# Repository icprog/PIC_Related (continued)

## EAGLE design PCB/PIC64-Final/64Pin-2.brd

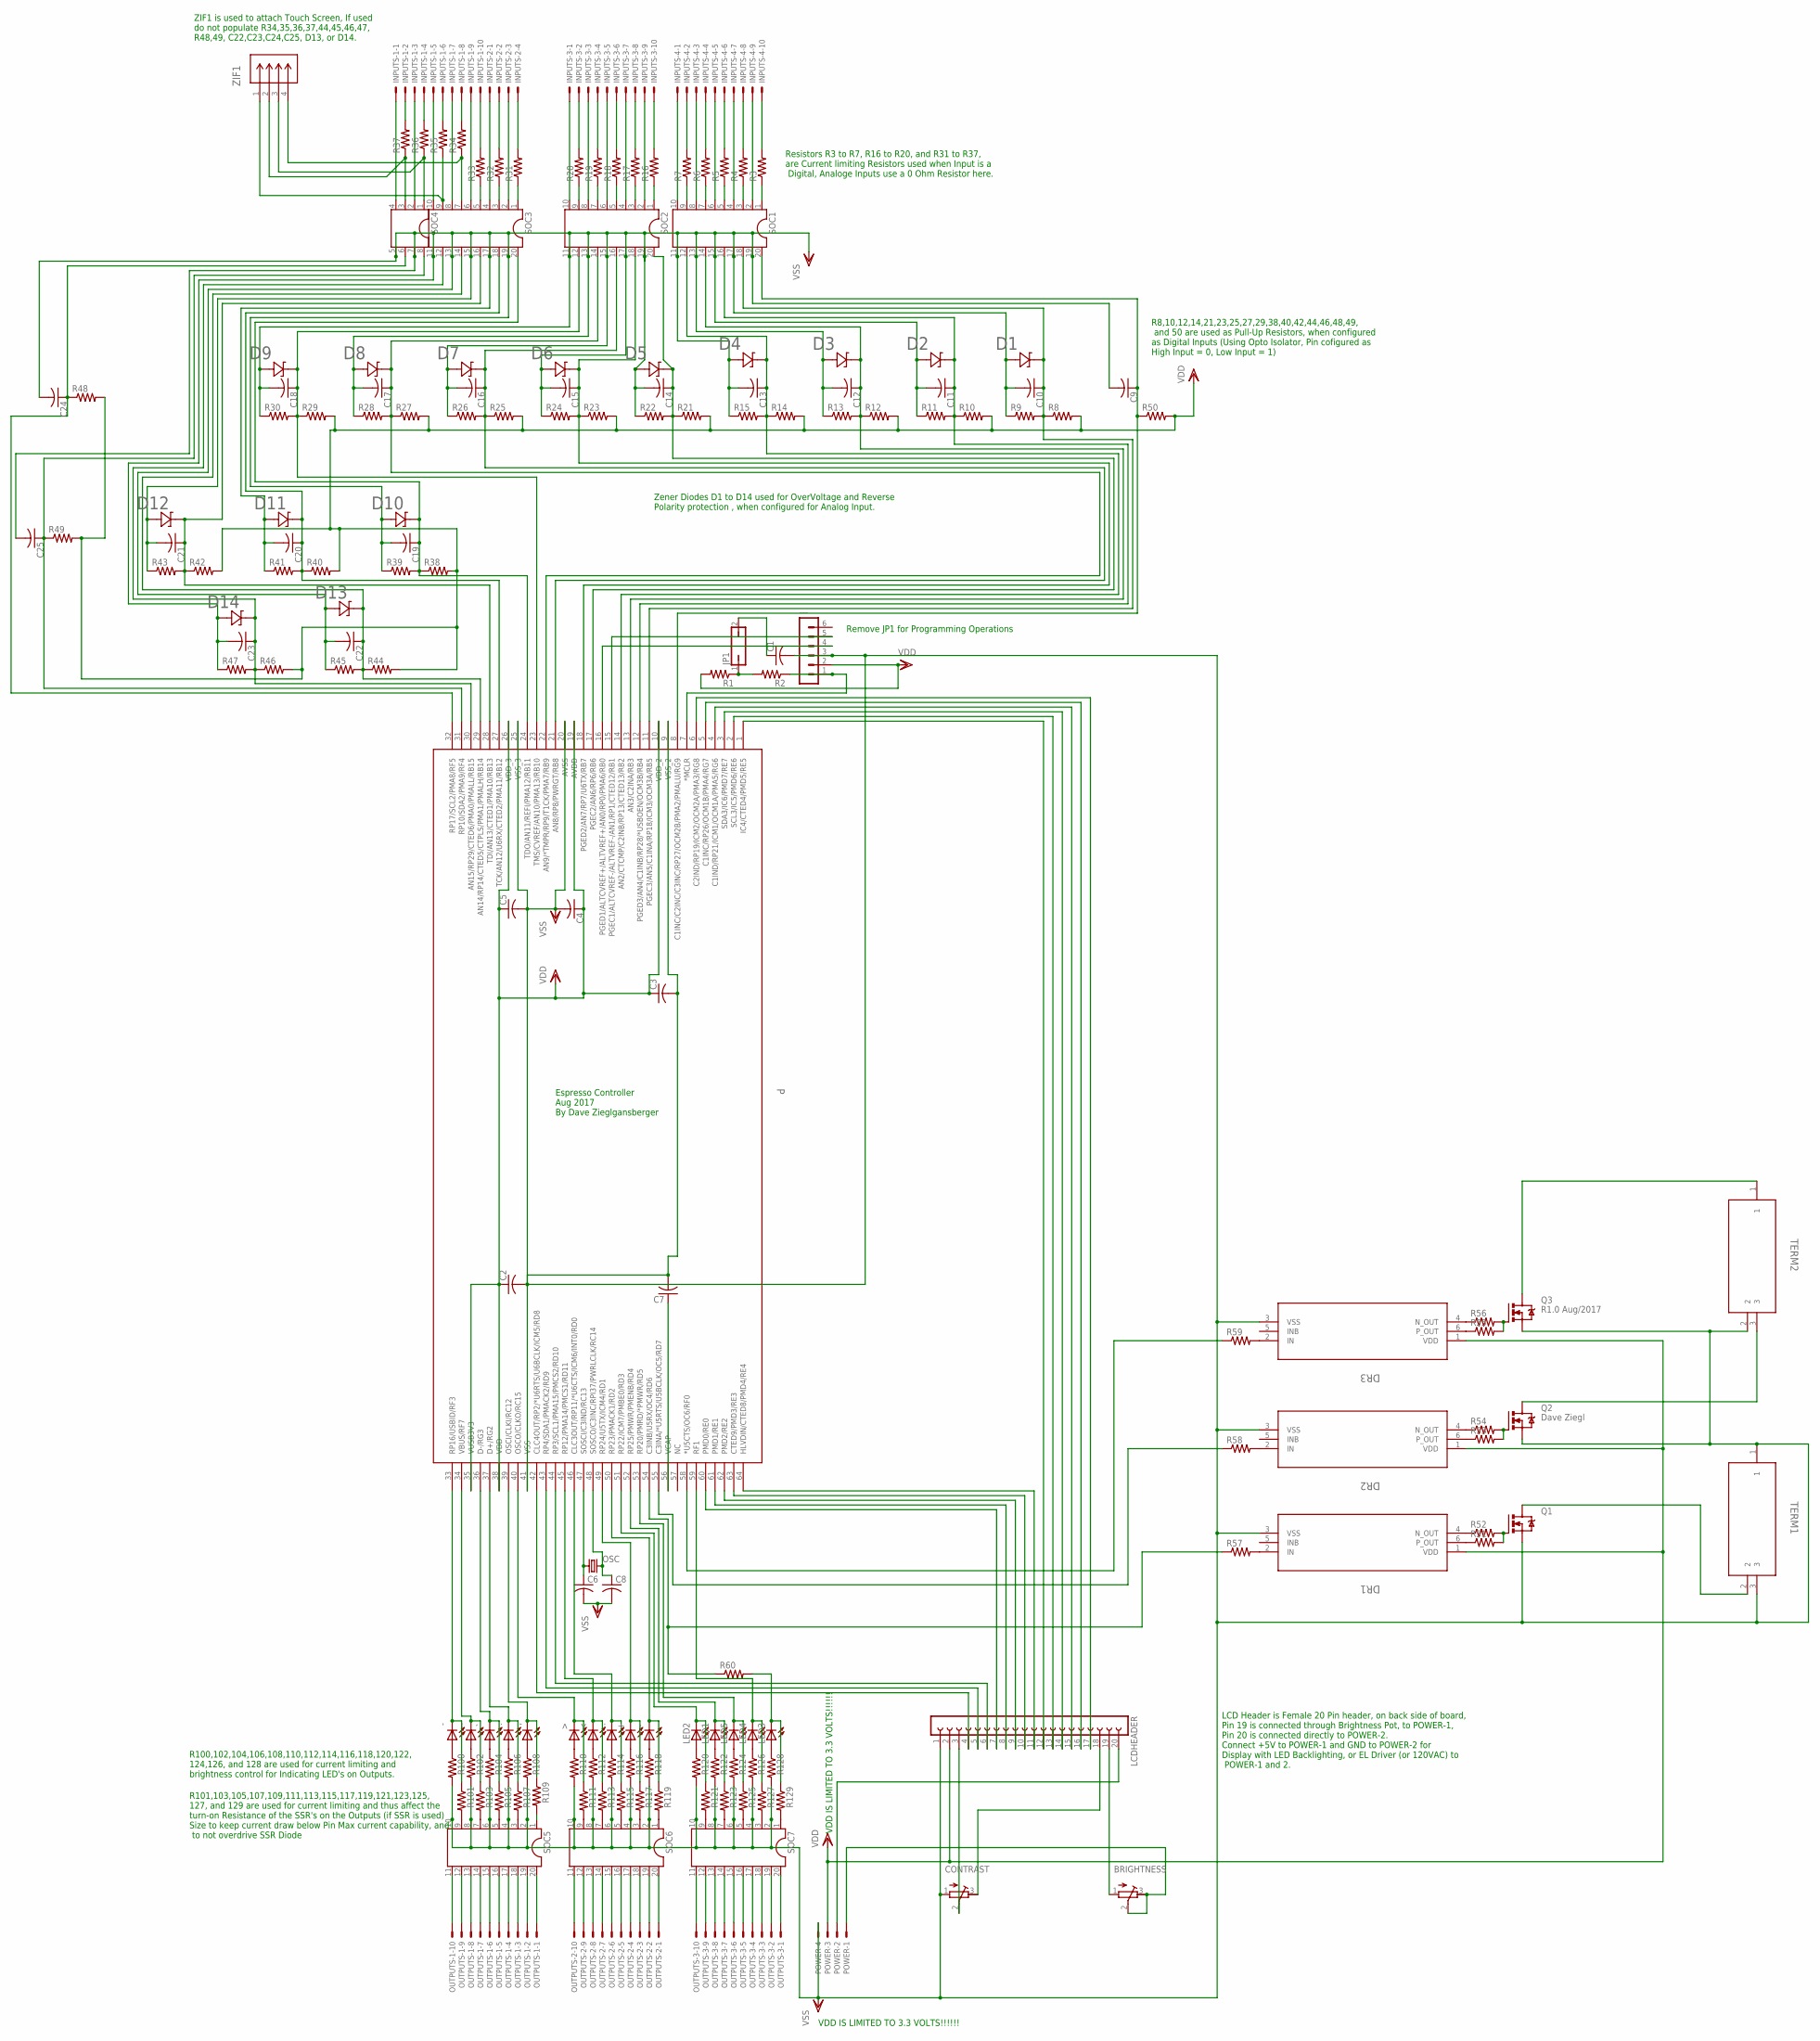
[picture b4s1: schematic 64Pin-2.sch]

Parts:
+: LED_SML0603
,: LED_SML0603
-: LED_SML0603
--: LED_SML0603
---: MA06-1
., ..: LED_SML0603
<: LED_SML0603
>: LED_SML0603
BRIGHTNESS: RTRIM3296W
C1, C2, C3, C4, C5, C6, C7, C8, C9, C10, C11, C12, C13, C14, C15, C16, C17, C18, C19, C20, C21, C22, C23, C24, C25: C0603
CONTRAST: RTRIM3296W
D1, D2, D3, D4, D5, D6, D7, D8, D9, D10, D11, D12, D13, D14: CZRU-M
DR1, DR2, DR3: MF06A
INPUTS-1, INPUTS-3, INPUTS-4: 22-23-2101
INPUTS-2: 22-23-2041
JP1: JP1
LCDHEADER: FE20
LED1, LED2, LED3, LED4, LED5: LED_SML0603
OSC: TC26H
OUTPUTS-1, OUTPUTS-2, OUTPUTS-3: 22-23-2101
P: TQFP64_10X10MC
POWER: 22-23-2041
Q1: TO220BV
Q2: Dave Ziegl; TO220BV
Q3: R1.0 Aug/2017; TO220BV
R1, R2, R3, R4, R5, R6, R7, R8, R9, R10, R11, R12, R13, R14, R15, R16, R17, R18, R19, R20, R21, R22, R23, R24, R25, R26, R27, R28, R29, R30, R31, R32, R33, R34, R35, R36, R37, R38, R39, R40, R41, R42, R43, R44, R45, R46, R47, R48, R49, R50, R51, R52, R53, R54, R55, R56, R57, R58, R59, R60, R100, R101, R102, R103, R104, R105, R106, R107, R108, R109, R110, R111, R112, R113, R114, R115, R116, R117, R118, R119, R120, R121, R122, R123, R124, R125, R126, R127, R128, R129: R0603
SOC1, SOC2, SOC3, SOC5, SOC6, SOC7: DIL20
SOC4: DIL08
TERM1, TERM2: 282837-3
ZIF1: 84952-4; CON4_SMT-RA_FCC-FPC2
`: LED_SML0603
~: LED_SML0603

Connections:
MCLR: ---.1, P.7 (*MCLR), R2.1
unnamed: INPUTS-1.1, SOC4.4
unnamed: R101.2, SOC5.9
unnamed: JP1.1, R1.1, R2.2
unnamed: INPUTS-1.2, R37.2
unnamed: R103.2, SOC5.7
unnamed: INPUTS-1.3, SOC4.2
unnamed: R105.2, SOC5.5
unnamed: INPUTS-1.4, R36.2
unnamed: R107.2, SOC5.3
unnamed: INPUTS-1.5, SOC3.10
unnamed: R36.1, SOC4.1, ZIF1.3
unnamed: C1.1, JP1.2
unnamed: R37.1, SOC4.3, ZIF1.2
unnamed: INPUTS-1.6, R35.2
unnamed: INPUTS-1.7, SOC3.8
unnamed: INPUTS-1.8, R34.2
unnamed: INPUTS-1.9, SOC3.6
unnamed: R109.2, SOC5.1
unnamed: INPUTS-1.10, R33.2
unnamed: INPUTS-2.1, SOC3.4
unnamed: INPUTS-2.2, R32.2
unnamed: INPUTS-2.3, SOC3.2
unnamed: INPUTS-2.4, R31.2
unnamed: DR2.4 (N_OUT), R54.1
unnamed: DR2.6 (P_OUT), R53.1
unnamed: DR1.4 (N_OUT), R52.1
unnamed: -.A, R100.1
unnamed: --.A, R102.1
unnamed: R104.1, `.A
unnamed: ..A, R106.1
unnamed: ,.A, R108.1
unnamed: DR1.6 (P_OUT), R51.1
unnamed: >.A, R110.1
unnamed: R111.2, SOC6.9
unnamed: INPUTS-4.5, SOC1.6
unnamed: INPUTS-4.4, R6.2
unnamed: Q3.D, TERM2.1
unnamed: R113.2, SOC6.7
unnamed: Q1.G, R51.2, R52.2
unnamed: R115.2, SOC6.5
unnamed: Q2.G, R53.2, R54.2
unnamed: R117.2, SOC6.3
unnamed: DR3.4 (N_OUT), R56.1
unnamed: R119.2, SOC6.1
unnamed: R6.1, SOC1.7
unnamed: R118.1, ~.A
unnamed: +.A, R116.1
unnamed: ...A, R114.1
unnamed: <.A, R112.1
unnamed: DR3.6 (P_OUT), R55.1
unnamed: R121.2, SOC7.9
unnamed: Q3.G, R55.2, R56.2
unnamed: R123.2, SOC7.7
unnamed: LCDHEADER.20, POWER.2
unnamed: R125.2, SOC7.5
unnamed: Q2.D, TERM2.3
unnamed: R127.2, SOC7.3
unnamed: R129.2, SOC7.1
unnamed: LED3.A, R128.1
unnamed: LED4.A, R126.1
unnamed: LED5.A, R124.1
unnamed: LED1.A, R122.1
unnamed: LED2.A, R120.1
unnamed: Q1.D, TERM1.2
unnamed: BRIGHTNESS.1 (A), LCDHEADER.19
unnamed: BRIGHTNESS.2 (S), BRIGHTNESS.3 (E), POWER.1
unnamed: DR1.2 (IN), R57.2
unnamed: DR2.2 (IN), R58.2
unnamed: DR3.2 (IN), R59.2
unnamed: P.55 (C3INA/*U5RTS/U5BCLK/OC5/RD7), R58.1
unnamed: P.58 (*U5CTS/OC6/RF0), R59.1
unnamed: R35.1, SOC3.9, ZIF1.1
unnamed: R34.1, SOC3.7, ZIF1.4
unnamed: R33.1, SOC3.5
unnamed: R32.1, SOC3.3
unnamed: R31.1, SOC3.1
unnamed: INPUTS-3.1, SOC2.10
unnamed: R20.1, SOC2.9
unnamed: INPUTS-3.3, SOC2.8
unnamed: INPUTS-3.2, R20.2
unnamed: INPUTS-3.4, R19.2
unnamed: INPUTS-3.5, SOC2.6
unnamed: R19.1, SOC2.7
unnamed: INPUTS-3.7, SOC2.4
unnamed: R17.1, SOC2.3
unnamed: INPUTS-3.8, R17.2
unnamed: INPUTS-3.9, SOC2.2
unnamed: R16.1, SOC2.1
unnamed: INPUTS-3.10, R16.2
unnamed: INPUTS-4.1, SOC1.10
unnamed: INPUTS-4.2, R7.2
unnamed: R7.1, SOC1.9
unnamed: INPUTS-4.3, SOC1.8
unnamed: R18.1, SOC2.5
unnamed: INPUTS-3.6, R18.2
unnamed: INPUTS-4.6, R5.2
unnamed: R5.1, SOC1.5
unnamed: INPUTS-4.7, SOC1.4
unnamed: INPUTS-4.8, R4.2
unnamed: R4.1, SOC1.3
unnamed: INPUTS-4.9, SOC1.2
unnamed: INPUTS-4.10, R3.2
unnamed: R3.1, SOC1.1
unnamed: CONTRAST.2 (S), LCDHEADER.3
unnamed: CONTRAST.3 (E), LCDHEADER.18
OUT: LED3.C, R60.2, R129.1
OUT1-1: OUTPUTS-1.10, SOC5.11
OUT1-2: OUTPUTS-1.9, SOC5.12
OUT2-1: OUTPUTS-1.8, SOC5.13
OUT2-2: OUTPUTS-1.7, SOC5.14
OUT3-1: OUTPUTS-1.6, SOC5.15
OUT3-2: OUTPUTS-1.5, SOC5.16
OUT4-1: OUTPUTS-1.4, SOC5.17
OUT4-2: OUTPUTS-1.3, SOC5.18
OUT5-1: OUTPUTS-1.2, SOC5.19
OUT5-2: OUTPUTS-1.1, SOC5.20
OUT6-1: OUTPUTS-2.10, SOC6.11
OUT6-2: OUTPUTS-2.9, SOC6.12
OUT7-1: OUTPUTS-2.8, SOC6.13
OUT7-2: OUTPUTS-2.7, SOC6.14
OUT8-1: OUTPUTS-2.6, SOC6.15
OUT8-2: OUTPUTS-2.5, SOC6.16
OUT9-1: OUTPUTS-2.4, SOC6.17
OUT9-2: OUTPUTS-2.3, SOC6.18
OUT10-1: OUTPUTS-2.2, SOC6.19
OUT10-2: OUTPUTS-2.1, SOC6.20
OUT11-1: OUTPUTS-3.10, SOC7.11
OUT11-2: OUTPUTS-3.9, SOC7.12
OUT12-1: OUTPUTS-3.8, SOC7.13
OUT12-2: OUTPUTS-3.7, SOC7.14
OUT13-1: OUTPUTS-3.6, SOC7.15
OUT13-2: OUTPUTS-3.5, SOC7.16
OUT14-1: OUTPUTS-3.4, SOC7.17
OUT14-2: OUTPUTS-3.3, SOC7.18
OUT15-1: OUTPUTS-3.2, SOC7.19
OUT15-2: OUTPUTS-3.1, SOC7.20
PGEC1: ---.5, P.15 (PGEC1/ALTCVREF-/ALTVREF-/AN1/RP1/CTED12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)
PGECD: ---.4, P.16 (PGED1/ALTCVREF+/ALTVREF+/AN0/RP0/PMA6/R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)
PIN1: LCDHEADER.12, P.1 (IC4/CTED4/PMD5/RE5)
PIN2: LCDHEADER.13, P.2 (SCL3/IC5/PMD6/RE6)
PIN3: LCDHEADER.14, P.3 (SDA3/IC6/PMD7/RE7)
PIN4: LCDHEADER.15, P.4 (C1IND/RP21/ICM1/OCM1A/PMA5/RG6)
PIN5: LCDHEADER.16, P.5 (C1INC/RP26/OCM1B/PMA4/RG7)
PIN6: LCDHEADER.17, P.6 (C2IND/RP19/ICM2/OCM2A/PMA3/RG8)
PIN8: C9.1, P.8 (C1INC/C2INC/C3INC/RP27/OCM2B/PMA2/PMALU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), R50.1, SOC1.20
PIN11: C10.1, D1.1 (11), P.11 (PGEC3/AN5/C1INA/RP18/ICM3/OCM3A/RB5), R8.1, R9.2, SOC1.18
PIN12: C11.1, D2.1 (11), P.12 (PGED3/AN4/C1INB/RP28/*USBOEN/OCM3B/RB4), R10.1, R11.2, SOC1.16
PIN13: C12.1, D3.1 (11), P.13 (AN3/C2INA/RB3), R12.1, R13.2, SOC1.14
PIN14: C13.1, D4.1 (11), P.14 (AN2/CTCMP/C2INB/RP13/CTED13/RB2), R14.1, R15.2, SOC1.12
PIN17: C14.1, D5.1 (11), P.17 (PGEC2/AN6/RP6/RB6), R21.1, R22.2, SOC2.20
PIN18: C15.1, D6.1 (11), P.18 (PGED2/AN7/RP7/U6TX/RB7), R23.1, R24.2, SOC2.18
PIN21: C16.1, D7.1 (11), P.21 (AN8/RP8/PWRGT/RB8), R25.1, R26.2, SOC2.16
PIN22: C17.1, D8.1 (11), P.22 (AN9/*TMPR/RP9/T1CK/PMA7/RB9), R27.1, R28.2, SOC2.14
PIN23: C18.1, D9.1 (11), P.23 (TMS/CVREF/AN10/PMA13/RB10), R29.1, R30.2, SOC2.12
PIN24: C19.1, D10.1 (11), P.24 (TDO/AN11/REFI/PMA12/RB11), R38.1, R39.2, SOC3.20
PIN27: C20.1, D11.1 (11), P.27 (TCK/AN12/U6RX/CTED2/PMA11/RB12), R40.1, R41.2, SOC3.18
PIN28: C21.1, D12.1 (11), P.28 (TDI/AN13/CTED1/PMA10/RB13), R42.1, R43.2, SOC3.16
PIN29: C22.1, D13.1 (11), P.29 (AN14/RP14/CTED5/CTPLS/PMA1/PMALH/RB14), R44.1, R45.2, SOC3.14
PIN30: C23.1, D14.1 (11), P.30 (AN15/RP29/CTED6/PMA0/PMALL/RB15), R46.1, R47.2, SOC3.12
PIN31: C25.1, P.31 (RP10/SDA2/PMA9/RF4), R49.1, SOC4.8
PIN32: C24.1, P.32 (RP17/SCL2/PMA8/RF5), R48.1, SOC4.6
PIN33: -.C, P.33 (RP16/USBID/RF3), R101.1
PIN34: --.C, P.34 (VBUS/RF7), R103.1
PIN36: P.36 (D-/RG3), R105.1, `.C
PIN37: ..C, P.37 (D+/RG2), R107.1
PIN39: ,.C, P.39 (OSCI/CLKI/RC12), R109.1
PIN40: >.C, P.40 (OSCO/CLKO/RC15), R111.1
PIN42: LCDHEADER.4, P.42 (CLC4OUT/RP2/*U6RTS/U6BCLK/ICM5/RD8)
PIN43: LCDHEADER.5, P.43 (RP4/SDA1/PMACK2/RD9)
PIN44: LCDHEADER.6, P.44 (RP3/SCL1/PMA15/PMCS2/RD10)
PIN45: <.C, P.45 (RP12/PMA14/PMCS1/RD11), R113.1
PIN46: ...C, P.46 (CLC3OUT/RP11/*U6CTS/ICM6/INT0/RD0), R115.1
PIN49: +.C, P.49 (RP24/U5TX/ICM4/RD1), R117.1
PIN50: P.50 (RP23/PMACK1/RD2), R119.1, ~.C
PIN51: LED2.C, P.51 (RP22/ICM7/PMBE0/RD3), R121.1
PIN52: LED1.C, P.52 (RP25/PMWR/PMENB/RD4), R123.1
PIN53: LED5.C, P.53 (RP20/PMRD/*PMWR/RD5), R125.1
PIN54: P.54 (C3INB/U5RX/OC4/RD6), R57.1, R60.1
PIN59: LED4.C, P.59 (RF1), R127.1
PIN60: LCDHEADER.7, P.60 (PMD0/RE0)
PIN61: LCDHEADER.8, P.61 (PMD1/RE1)
PIN62: LCDHEADER.9, P.62 (PMD2/RE2)
PIN63: LCDHEADER.10, P.63 (CTED9/PMD3/RE3)
PIN64: LCDHEADER.11, P.64 (HLVDIN/CTED8/PMD4/RE4)
SOSCI: C6.1, OSC.1, P.47 (SOSCI/C3IND/RC13)
SOSCO: C8.1, OSC.2, P.48 (SOSCO/C3INC/RPI37/PWRLCLK/RC14)
VCAP: C7.1, P.56 (VCAP)
VDD: ---.2, C2.1, C3.1, C4.1, C5.1, DR1.1 (VDD), DR2.1 (VDD), DR3.1 (VDD), LCDHEADER.2, P.10 (VDD_2), P.19 (AVDD), P.26 (VDD_3), P.35 (VUSB3V3), P.38 (VDD), POWER.3, R1.2, R8.2, R10.2, R12.2, R14.2, R21.2, R23.2, R25.2, R27.2, R29.2, R38.2, R40.2, R42.2, R44.2, R46.2, R48.2, R49.2, R50.2
VSS: ---.3, C1.2, C2.2, C3.2, C4.2, C5.2, C6.2, C7.2, C8.2, C9.2, C10.2, C11.2, C12.2, C13.2, C14.2, C15.2, C16.2, C17.2, C18.2, C19.2, C20.2, C21.2, C22.2, C23.2, C24.2, C25.2, CONTRAST.1 (A), D1.2 (22), D2.2 (22), D3.2 (22), D4.2 (22), D5.2 (22), D6.2 (22), D7.2 (22), D8.2 (22), D9.2 (22), D10.2 (22), D11.2 (22), D12.2 (22), D13.2 (22), D14.2 (22), DR1.3 (VSS), DR2.3 (VSS), DR3.3 (VSS), LCDHEADER.1, P.9 (VSS_2), P.20 (AVSS), P.25 (VSS_3), P.41 (VSS), POWER.4, Q1.S, Q2.S, Q3.S, R9.1, R11.1, R13.1, R15.1, R22.1, R24.1, R26.1, R28.1, R30.1, R39.1, R41.1, R43.1, R45.1, R47.1, R100.2, R102.2, R104.2, R106.2, R108.2, R110.2, R112.2, R114.2, R116.2, R118.2, R120.2, R122.2, R124.2, R126.2, R128.2, SOC1.11, SOC1.13, SOC1.15, SOC1.17, SOC1.19, SOC2.11, SOC2.13, SOC2.15, SOC2.17, SOC2.19, SOC3.11, SOC3.13, SOC3.15, SOC3.17, SOC3.19, SOC4.5, SOC4.7, SOC5.2, SOC5.4, SOC5.6, SOC5.8, SOC5.10, SOC6.2, SOC6.4, SOC6.6, SOC6.8, SOC6.10, SOC7.2, SOC7.4, SOC7.6, SOC7.8, SOC7.10, TERM1.1, TERM1.3, TERM2.2

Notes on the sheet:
Espresso Controller Aug 2017 By Dave Zieglgansberger
Resistors R3 to R7, R16 to R20, and R31 to R37, are Current limiting Resistors used when Input is a Digital, Analoge Inputs use a 0 Ohm Resistor here.
Remove JP1 for Programming Operations
Zener Diodes D1 to D14 used for OverVoltage and Reverse Polarity protection , when configured for Analog Input.
ZIF1 is used to attach Touch Screen, If used do not populate R34,35,36,37,44,45,46,47, R48,49, C22,C23,C24,C25, D13, or D14.
R8,10,12,14,21,23,25,27,29,38,40,42,44,46,48,49, and 50 are used as Pull-Up Resistors, when configured as Digital Inputs (Using Opto Isolator, Pin cofigured as High Input = 0, Low Input = 1)
LCD Header is Female 20 Pin header, on back side of board, Pin 19 is connected through Brightness Pot, to POWER-1, Pin 20 is connected directly to POWER-2. Connect +5V to POWER-1 and GND to POWER-2 for Display with LED Backlighting, or EL Driver (or 120VAC) to POWER-1 and 2.
R100,102,104,106,108,110,112,114,116,118,120,122, 124,126, and 128 are used for current limiting and brightness control for Indicating LED's on Outputs.
R101,103,105,107,109,111,113,115,117,119,121,123,125, 127, and 129 are used for current limiting and thus affect the turn-on Resistance of the SSR's on the Outputs (if SSR is used) Size to keep current draw below Pin Max current capability, and to not overdrive SSR Diode
VDD IS LIMITED TO 3.3 VOLTS!!!!!!

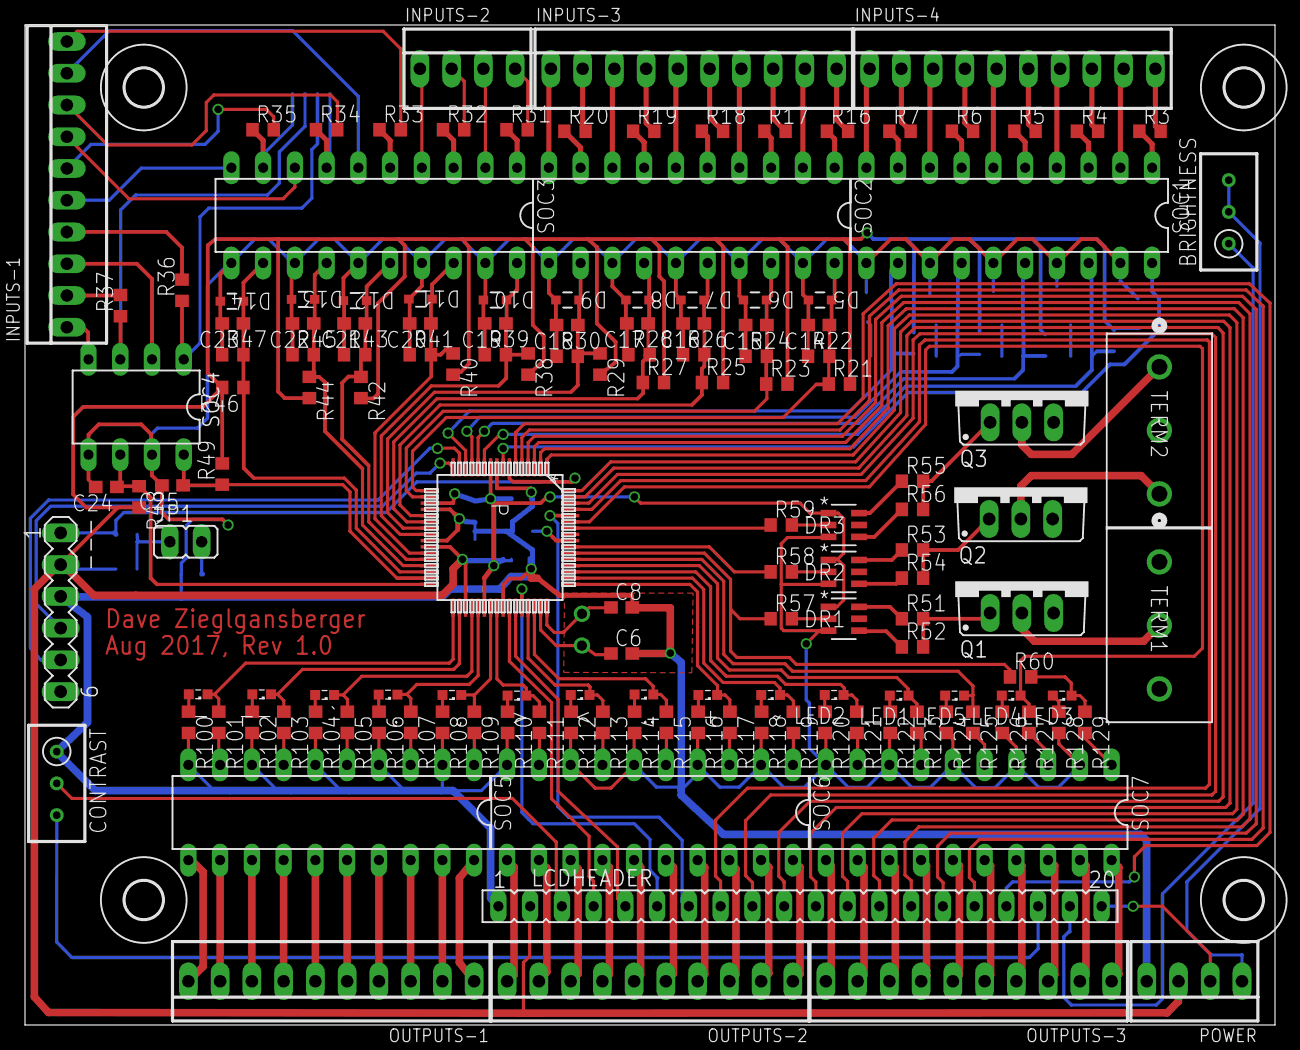
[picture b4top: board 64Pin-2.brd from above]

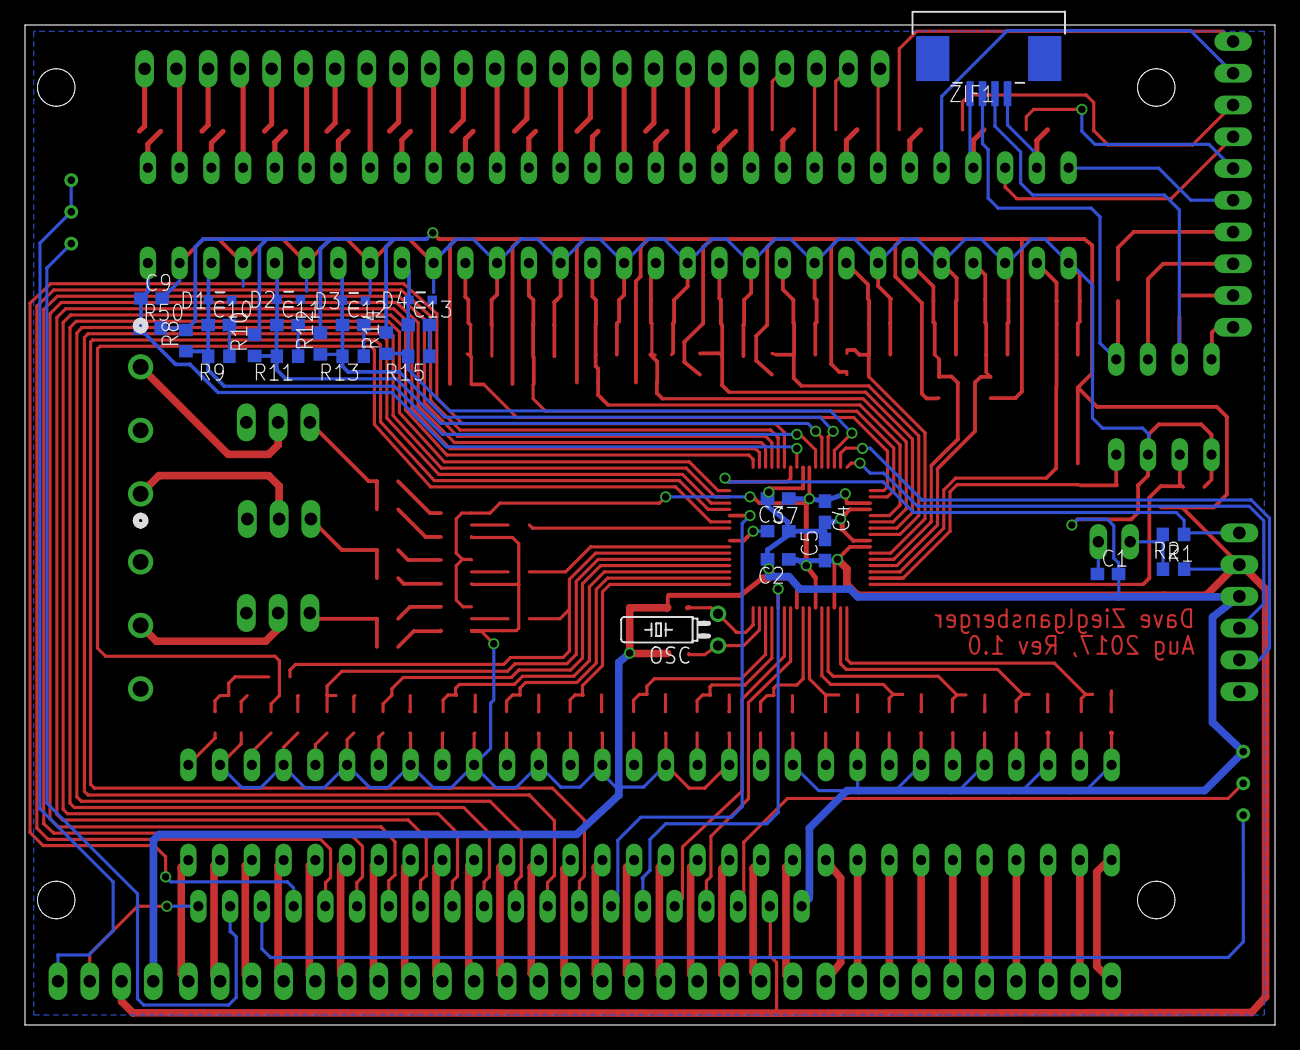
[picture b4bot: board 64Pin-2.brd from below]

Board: 2 copper layers, 100.0 x 80.0 mm, 179 parts (28 on the bottom side), 190 nets.

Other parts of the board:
U$5, U$6, U$7, U$8: 3,0

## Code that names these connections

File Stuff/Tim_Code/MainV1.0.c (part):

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void (display_ADC_count_on_LEDs)(int temp){
    
if (temp > 150){
    RB0 = 1;
} 
else RB0 = 0;

if (temp > 300){
    RB1 = 1;
} 
else RB1 = 0;

if (temp > 450){
    RB2 = 1;
} 
else RB2 = 0;

if (temp > 600){
    RB3 = 1;
} 
else RB3 = 0;

if (temp > 750){
    RB4 = 1;
} 
else RB4 = 0;    
    
if (temp > 1000){
//    RB5 = 1;
} 
//else RB5 = 0;    
    
    
    
}
void display_temperature_on_LEDs(float temp){
if (temp > 200){
    RB0 = 1;
} 
else RB0 = 0;

if (temp > 220){
    RB1 = 1;
} 
else RB1 = 0;

if (temp > 240){
    RB2 = 1;
} 
else RB2 = 0;

if (temp > 260){
    RB3 = 1;
} 
else RB3 = 0;

if (temp > 280){
    RB4 = 1;
} 
else RB4 = 0;    
    
if (temp > 300){
//    RB5 = 1;
} 
//else RB5 = 0;    
    
    
    
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
void display_temperature_on_LEDs2(float temp){
if (temp > 230){
    RB0 = 1;
} 
else RB0 = 0;

if (temp > 240){
    RB1 = 1;
} 
else RB1 = 0;

if (temp > 250){
    RB2 = 1;
} 
else RB2 = 0;

if (temp > 260){
    RB3 = 1;
} 
else RB3 = 0;

if (temp > 270){
    RB4 = 1;
} 
else RB4 = 0;    
    
if (temp > 280){
//    RB5 = 1;
} 
//else RB5 = 0;    
    
    
    
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    char dummy_char = 0;
    temp = temp / 10;
    byte_1 = (char) temp;
//   RC0 = 0; 
   __delay_us(100);
   dummy_char = (SPI_TRANSFER)(byte_1);
   __delay_us(100);
//   RC0 = 1;


}
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    
    //Beginning of RA4 input Switch debounce code
    if ((RA4 == 0) && (button_array[0][3] == 0)){  //0 equals button depressed and button_array[0][3] is for off bit latch
        button_array[0][2] = 1; //[x][y] x = switch 1(RA4) y = on bit active (switch one latched or active)
    }
    if (button_array[0][2] == 1){
        button_array[0][0]++;   //[x][y] x = switch 1(RA4) y = latched on timer
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        }
    }
    if ((button_array[0][0] > 5) && (RA4 == 1)){ //check if latched on timer has expired and button no longer depressed
        button_array[0][2] = 0; //turn off active button depression for RA4
        button_array[0][0] = 0; //reset latch on timer
        button_array[0][3] = 1; //[x][y] x = switch 1(RA4) y = off bit active (switch one not active)
        button_array[0][1] = 0; //reset off timer        
    }
    if (button_array[0][3] == 1){
        button_array[0][1]++;   //increment button off timer
    }
    if (button_array[0][1] > 5){
        button_array[0][3] = 0; //[x][y] x = switch 1(RA4) y = off bit active (switch one not active)
    }
//End of RA4 Switch debounce code

    //Beginning of RA5 input Switch debounce code
    if ((RA5 == 0) && (button_array[1][3] == 0)){  //0 equals button depressed and button_array[0][3] is for off bit latch
        button_array[1][2] = 1; //[x][y] x = switch 2(RA5) y = on bit active (switch one latched or active)
    }
    if (button_array[1][2] == 1){
        button_array[1][0]++;   //[x][y] x = switch 2(RA5) y = latched on timer
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        }
    }
    if ((button_array[1][0] > 5) && (RA5 == 1)){ //check if latched on timer has expired and button no longer depressed
        button_array[1][2] = 0; //turn off active button depression for RA4
        button_array[1][0] = 0; //reset latch on timer
        button_array[1][3] = 1; //[x][y] x = switch 2(RA5) y = off bit active (switch one not active)
        button_array[1][1] = 0; //reset off timer        
    }
    if (button_array[1][3] == 1){
        button_array[1][1]++;   //increment button off timer
    }
    if (button_array[1][1] > 5){
        button_array[1][3] = 0; //[x][y] x = switch 2(RA5) y = off bit active (switch one not active)
    }
//End of RA5 Switch debounce code
    
    //Beginning of RA7 input Switch debounce code
    if ((RA7 == 0) && (button_array[2][3] == 0)){  //0 equals button depressed and button_array[0][3] is for off bit latch
        button_array[2][2] = 1; //[x][y] x = switch 3(RA7) y = on bit active (switch one latched or active)
    }
    if (button_array[2][2] == 1){
        button_array[2][0]++;   //[x][y] x = switch 3(RA7) y = latched on timer
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        }
    }
    if ((button_array[2][0] > 10) && (RA7 == 1)){ //check if latched on timer has expired and button no longer depressed
        button_array[2][2] = 0; //turn off active button depression for RA7
        button_array[2][0] = 0; //reset latch on timer
        button_array[2][3] = 1; //[x][y] x = switch 3(RA7) y = off bit active (switch one not active)
        button_array[2][1] = 0; //reset off timer        
    }
    if (button_array[2][3] == 1){
        button_array[2][1]++;   //increment button off timer
    }
    if (button_array[2][1] > 10){
        button_array[2][3] = 0; //[x][y] x = switch 3(RA7) y = off bit active (switch one not active)
    }
//End of RA5 Switch debounce code


    if (button_array[2][2] == 1){
        RB4 = 1;
    }
    else RB4 = 0;
    
    
    
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void set_alarm_point(void){
 
    if (button_array[0][2] == 1){   //check button RA4
        RC0 = 0;
        __delay_us(100);
        format_temp_to_send(H_alarm_point_array[0][0]);
        RC0 = 1;
        __delay_us(100);
        if ((button_array[1][2] == 1) && (H_alarm_point_array[0][2] < 1)){
            H_alarm_point_array[0][0] = H_alarm_point_array[0][0] + 10; //10 is equal to 1 degree
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IO_Initialize();
spi_init();
ADCC_Initialize();
RC7 = 1;    //Thermistor power    
while (1){
    program_cycles++;
    
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        RB5 = 1 - RB5;  //toggle LED
        program_cycles = 0;
    }
 //   RC7 = 1;    //Thermistor power
//    temp0 = ADCRead(3);
//     temp0 = 1023 - temp0;
//    temp_in_degree_C = tempCalc(temp0);
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        final_temps[0] = average_temps(temp_array0);
    }
    if ((program_cycles == 50) && (button_array[0][2] == 0)){
        RC0 = 0;    //SS for Display 0
         __delay_us(80);
        format_temp_to_send(final_temps[0]);
        RC0 = 1;    //SS for Display 0
        __delay_us(80);
    }
    if (program_cycles == 60){
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        final_temps[1] = average_temps(temp_array1);
    }
    if (program_cycles == 100){
        RC1 = 0;    //SS for Display 1
        __delay_us(80);
        format_temp_to_send(final_temps[1]);
        RC1 = 1;    //SS for Display 1
         __delay_us(80);
    }
    if (program_cycles == 110){
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        final_temps[2] = average_temps(temp_array2);
    }
    if (program_cycles == 150){
        RC2 = 0;    //SS for Display 2
        __delay_us(80);
        format_temp_to_send(final_temps[2]);
        RC2 = 1;    //SS for Display 2
         __delay_us(80);
    }
    if (program_cycles == 160){
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        final_temps[3] = average_temps(temp_array3);
    }
    if (program_cycles == 200){
        RC6 = 0;    //SS for Display 3
         __delay_us(80);
        format_temp_to_send(final_temps[3]);
        RC6 = 1;    //SS for Display 3
         __delay_us(80);
    }

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//    display_ADC_count_on_LEDs(temp0);
//    display_temperature_on_LEDs2(temp_in_degree_C);
//    display_temperature_on_LEDs2(final_temps[0]);
//   RC0 = 0; 
//   __delay_us(100);
//   test_char = (SPI_TRANSFER)('U');
//   __delay_us(100);
//   RC0 = 1;
//   if (test_char == 'U'){
//       RB5 = 1;
//   }
//   else RB5 = 0;
//   __delay_us(10000);
//   __delay_us(10000);
//    RB0 = 0;
//    RB1 = 0;
//    RB2 = 0;
//    RB3 = 0;
//    RB4 = 0;
//    RB5 = 1;
        
   
}
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
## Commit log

2018-09-13 Initial Commit, Transferred to New Repo
    GitHub fucked up, kept erroring out, transferred all to new Repo, hope it fixes problem
2018-09-13 Initial Commit New Repo
2018-09-13 Temporary Show Faults on display
2018-09-13 KS0108 Stuff
2018-09-14 Fixed GroupHead Temperature control, now holds within .2 DegF
2018-09-14 Cleanup main display
2018-09-14 Charger Tuning
2018-09-14 n
    n
2018-09-14 GitIgnore Update
2018-09-14 Remove
2018-09-14 Git Ignore Update
